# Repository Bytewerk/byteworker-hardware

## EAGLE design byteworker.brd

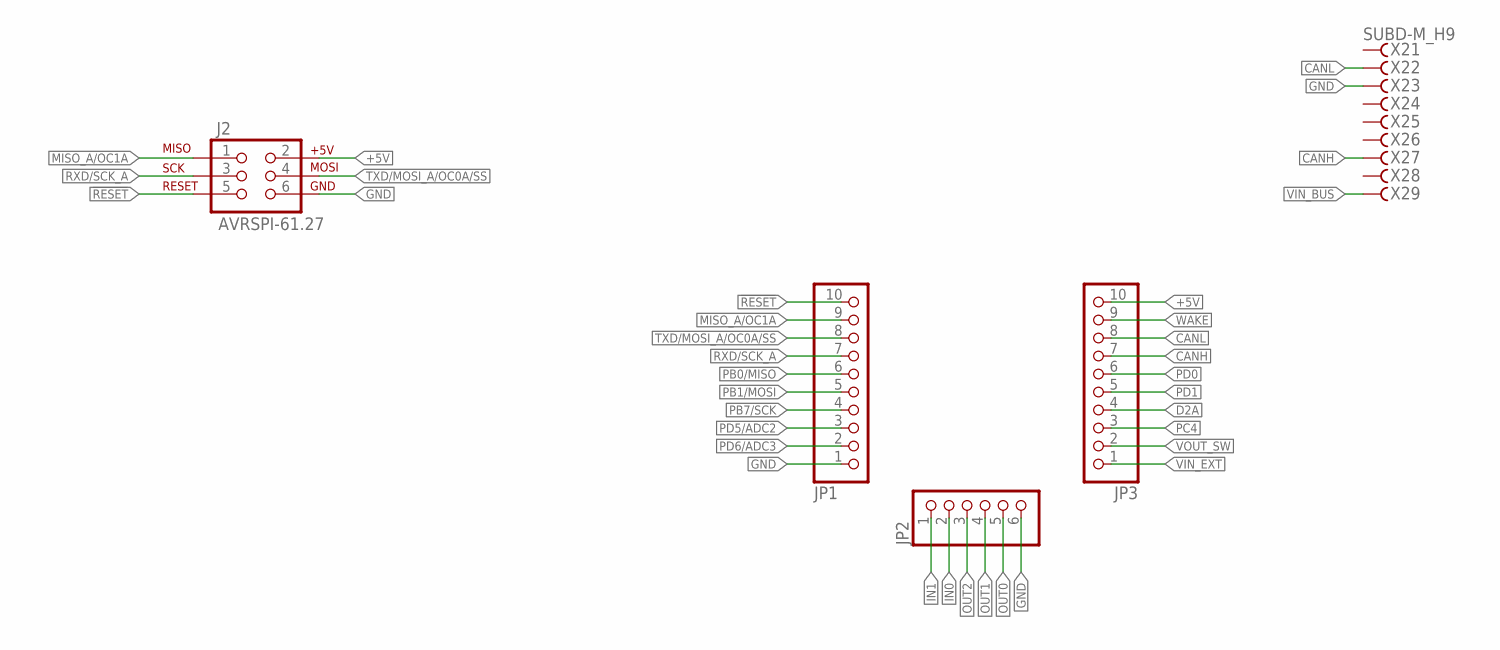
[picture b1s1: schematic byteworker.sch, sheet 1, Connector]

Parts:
J2: AVRSPI-61.27; 2X3-1.27
JP1, JP3: PINHD-1X10; 1X10
JP2: PINHD-1X6; 1X06
X2: SUBD-M_H9; SUBD9

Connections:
!RESET!: J2.5 (RESET), JP1.10; also elsewhere on the board
+5V: J2.2 (+5V), JP3.10; also elsewhere on the board
CANH: JP3.7, X2.8; also elsewhere on the board
CANL: JP3.8, X2.4; also elsewhere on the board
D2A: JP3.4; also elsewhere on the board
GND: J2.6 (GND), JP1.1, JP2.6, X2.3; also elsewhere on the board
IN0: JP2.2; also elsewhere on the board
IN1: JP2.1; also elsewhere on the board
MISO_A/OC1A: J2.1 (MISO), JP1.9; also elsewhere on the board
OUT0: JP2.5; also elsewhere on the board
OUT1: JP2.4; also elsewhere on the board
OUT2: JP2.3; also elsewhere on the board
PB0/MISO: JP1.6; also elsewhere on the board
PB1/MOSI: JP1.5; also elsewhere on the board
PB7/SCK: JP1.4; also elsewhere on the board
PC4: JP3.3; also elsewhere on the board
PD0: JP3.6; also elsewhere on the board
PD1: JP3.5; also elsewhere on the board
PD5/ADC2: JP1.3; also elsewhere on the board
PD6/ADC3: JP1.2; also elsewhere on the board
RXD/SCK_A: J2.3 (SCK), JP1.7; also elsewhere on the board
TXD/MOSI_A/OC0A/SS: J2.4 (MOSI), JP1.8; also elsewhere on the board
VIN_BUS: X2.6; also elsewhere on the board
VIN_EXT: JP3.1; also elsewhere on the board
VOUT_SW: JP3.2; also elsewhere on the board
WAKE: JP3.9; also elsewhere on the board

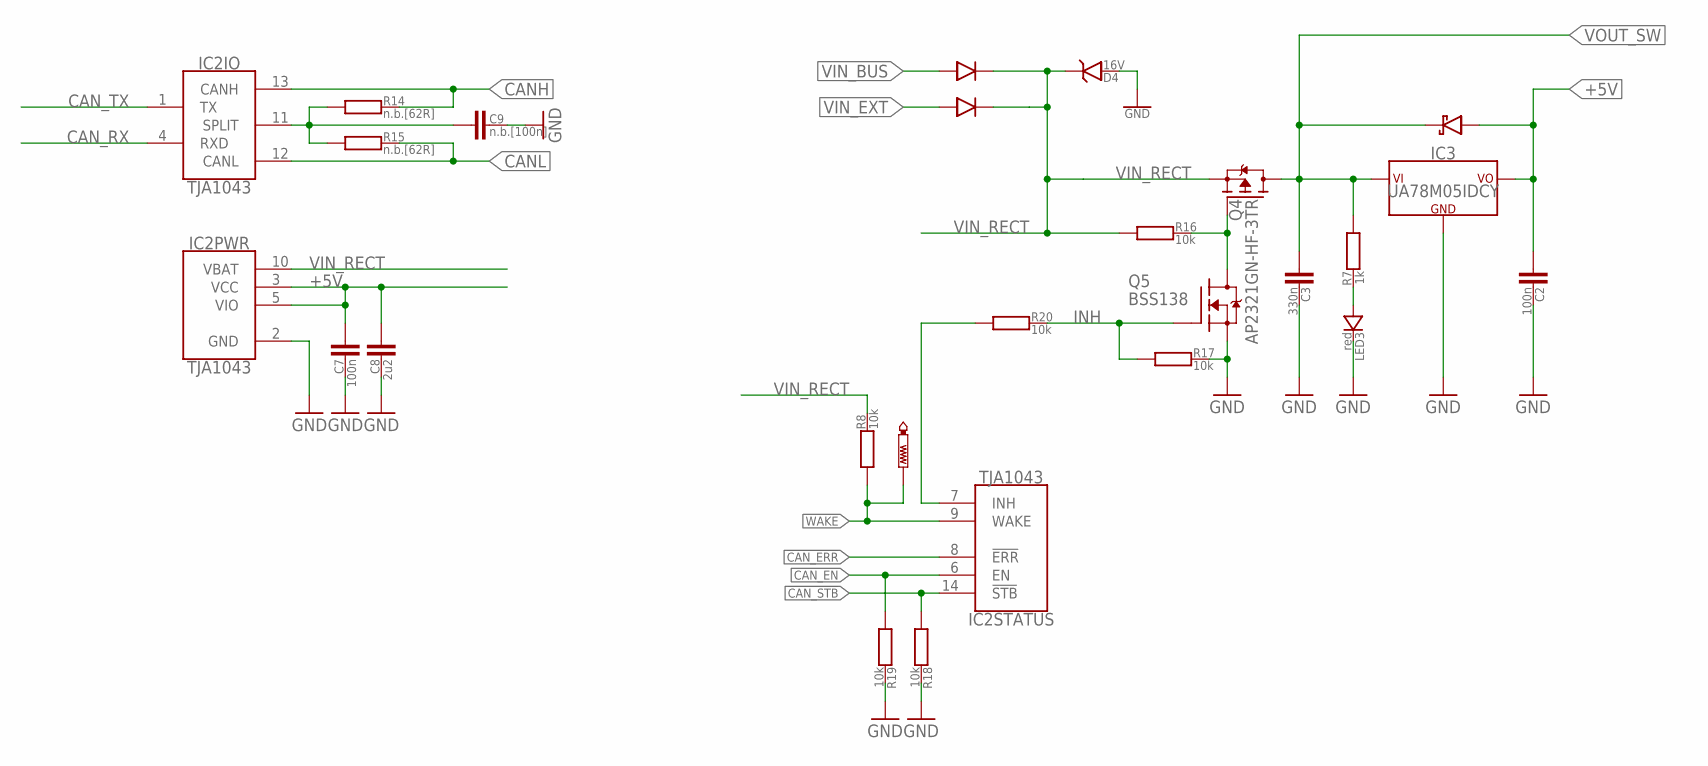
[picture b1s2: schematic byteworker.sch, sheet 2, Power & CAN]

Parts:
C2, C7: 100n; C0603
C3: 330n; C0603
C8: 2u2; C0805
C9: n.b.[100n]; C0603
D1, D5: 1N5819HW; SOD123
D4: 16V; SOD-128
D6: SCHOTTKY323; SOD323
IC2: TJA1043; SO14
IC3: UA78M05IDCY; SOT223
LED3: red; LED0603
Q4: AP2321GN-HF-3TR; SOT23-3
Q5: BSS138; SOT23C
R7: 1k; R0603
R8, R16, R17, R18, R19, R20: 10k; R0603
R14, R15: n.b.[62R]; R0603
TP2: PTR1B1,27; B1,27

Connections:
!CAN_ERR!: IC2.8 (!ERR!); also elsewhere on the board
!CAN_STB!: IC2.14 (!STB!), R18.1; also elsewhere on the board
+5V: C2.1, C7.1, C8.1, D6.A, IC2.3 (VCC), IC2.5 (VIO), IC3.3 (+5V); also elsewhere on the board
CANH: IC2.13 (CANH), R14.2; also elsewhere on the board
CANL: IC2.12 (CANL), R15.2; also elsewhere on the board
CAN_EN: IC2.6 (EN), R19.1; also elsewhere on the board
CAN_RX: IC2.4 (RXD); also elsewhere on the board
CAN_TX: IC2.1 (TX); also elsewhere on the board
GND: C2.2, C3.2, C7.2, C8.2, C9.2, D4.A, IC2.2 (GND), IC3.2 (GND), IC3.4 (GND), LED3.C, Q5.2 (S), R17.2, R18.2, R19.2; also elsewhere on the board
INH: Q5.1 (G), R17.1, R20.2
unnamed: C9.1, IC2.11 (SPLIT), R14.1, R15.1
unnamed: IC2.7 (INH), R20.1
unnamed: Q4.1 (G), Q5.3 (D), R16.2
unnamed: LED3.A, R7.2
VIN_BUS: D5.A; also elsewhere on the board
VIN_EXT: D1.A; also elsewhere on the board
VIN_RECT: D1.C, D4.C, D5.C, IC2.10 (VBAT), Q4.2 (S), R8.2, R16.1; also elsewhere on the board
VOUT_SW: C3.1, D6.C, IC3.1 (VIN), Q4.3 (D), R7.1; also elsewhere on the board
WAKE: IC2.9 (WAKE), R8.1, TP2.TP; also elsewhere on the board

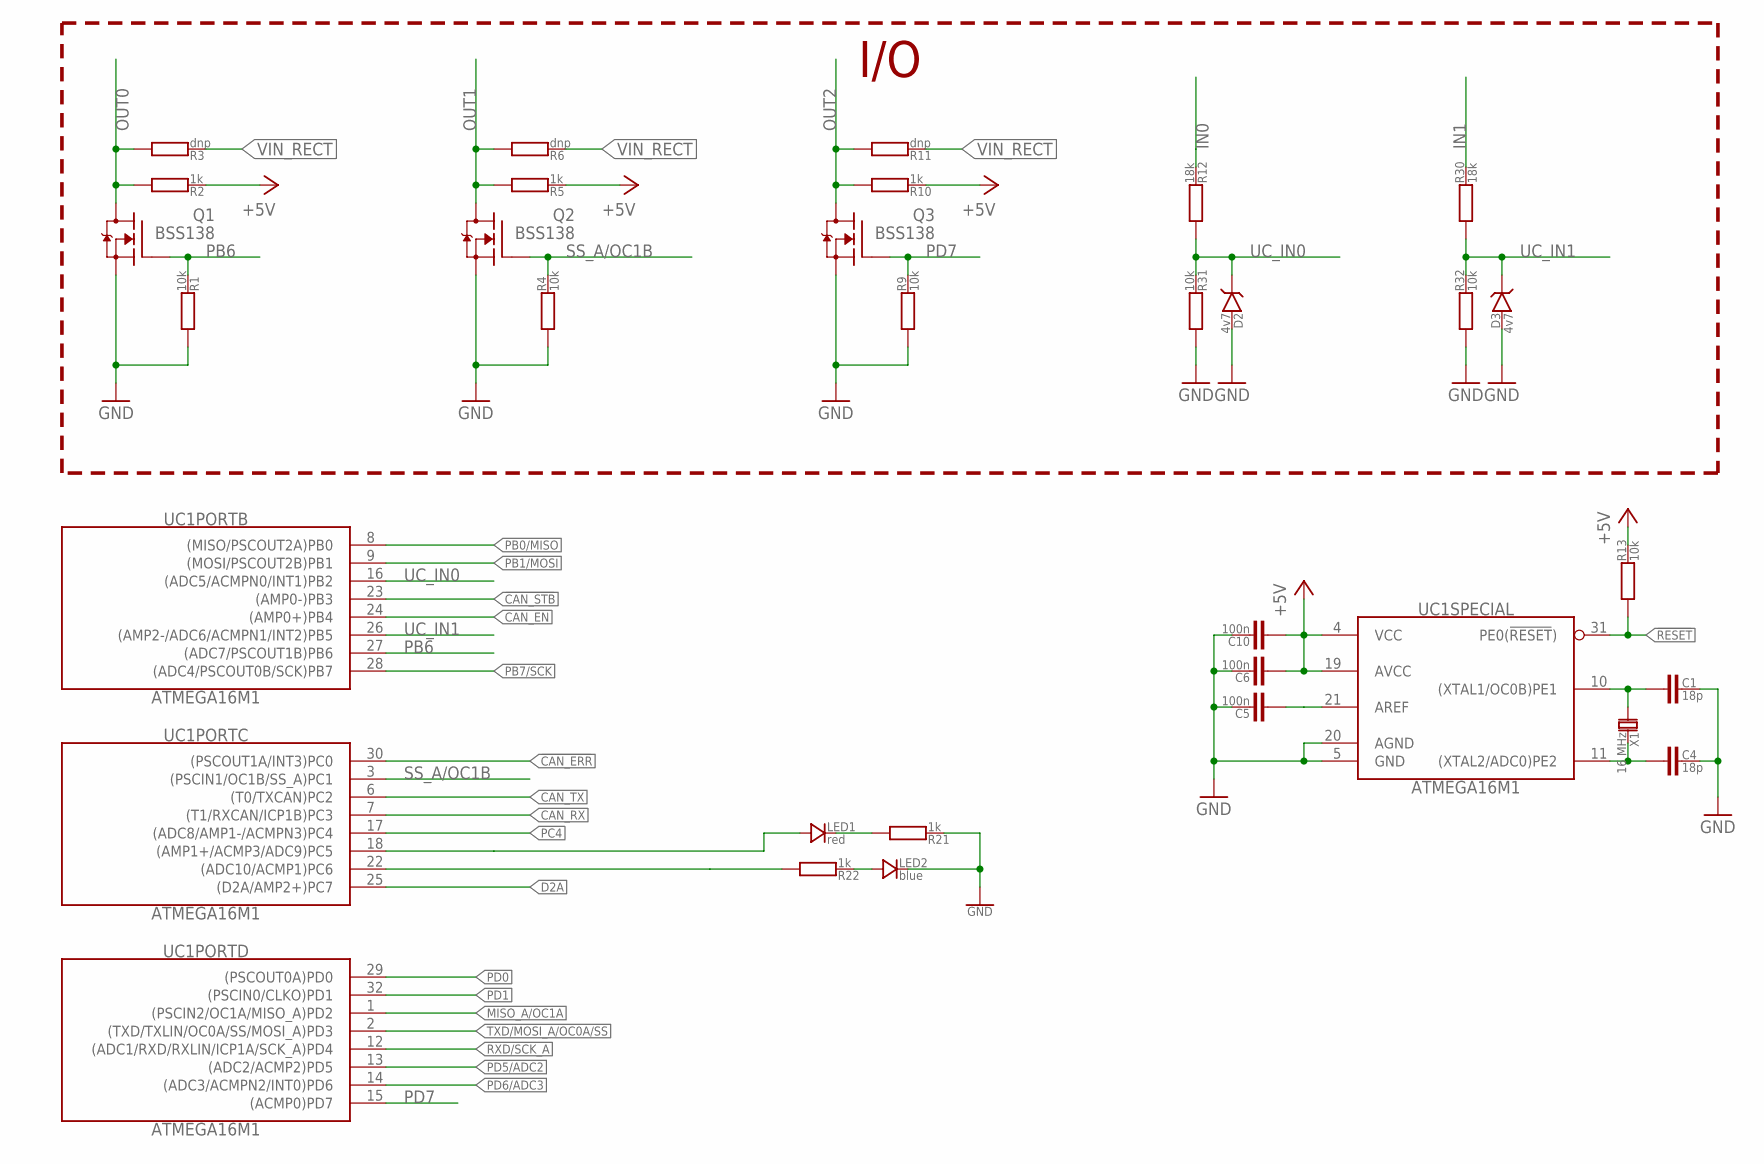
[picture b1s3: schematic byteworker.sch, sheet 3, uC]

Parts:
C1, C4: 18p; C0603
C5, C6, C10: 100n; C0603
D2, D3: 4v7; SOD80
LED1: red; LED0603
LED2: blue; LED0603
Q1, Q2, Q3: BSS138; SOT23C
R1, R4, R9, R13, R31, R32: 10k; R0603
R2, R5, R10, R21, R22: 1k; R0603
R3, R6, R11: dnp; R0603
R12, R30: 18k; R0603
UC1: ATMEGA16M1; TQFP32-08
X1: 16 MHz; 5.0X3.2

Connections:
!CAN_ERR!: UC1.30 ((PSCOUT1A/INT3)PC0); also elsewhere on the board
!CAN_STB!: UC1.23 ((AMP0-)PB3); also elsewhere on the board
!RESET!: R13.1, UC1.31 (PE0(!RESET!)); also elsewhere on the board
+5V: C6.1, C10.1, R2.2, R5.2, R10.2, R13.2, UC1.4 (VCC), UC1.19 (AVCC); also elsewhere on the board
AREF: C5.1, UC1.21 (AREF)
CAN_EN: UC1.24 ((AMP0+)PB4); also elsewhere on the board
CAN_RX: UC1.7 ((T1/RXCAN/ICP1B)PC3); also elsewhere on the board
CAN_TX: UC1.6 ((T0/TXCAN)PC2); also elsewhere on the board
D2A: UC1.25 ((D2A/AMP2+)PC7); also elsewhere on the board
GND: C1.2, C4.2, C5.2, C6.2, C10.2, D2.A, D3.A, LED2.C, Q1.2 (S), Q2.2 (S), Q3.2 (S), R1.1, R4.1, R9.1, R21.2, R31.1, R32.1, UC1.5 (GND), UC1.20 (AGND); also elsewhere on the board
IN0: R12.2; also elsewhere on the board
IN1: R30.2; also elsewhere on the board
MISO_A/OC1A: UC1.1 ((PSCIN2/OC1A/MISO_A)PD2); also elsewhere on the board
unnamed: C1.1, UC1.10 ((XTAL1/OC0B)PE1), X1.1
unnamed: C4.1, UC1.11 ((XTAL2/ADC0)PE2), X1.2
unnamed: LED2.A, R22.2
unnamed: LED1.A, UC1.18 ((AMP1+/ACMP3/ADC9)PC5)
unnamed: LED1.C, R21.1
OUT0: Q1.3 (D), R2.1, R3.1; also elsewhere on the board
OUT1: Q2.3 (D), R5.1, R6.1; also elsewhere on the board
OUT2: Q3.3 (D), R10.1, R11.1; also elsewhere on the board
PB0/MISO: UC1.8 ((MISO/PSCOUT2A)PB0); also elsewhere on the board
PB1/MOSI: UC1.9 ((MOSI/PSCOUT2B)PB1); also elsewhere on the board
PB6: Q1.1 (G), R1.2, UC1.27 ((ADC7/PSCOUT1B)PB6)
PB7/SCK: UC1.28 ((ADC4/PSCOUT0B/SCK)PB7); also elsewhere on the board
PC4: UC1.17 ((ADC8/AMP1-/ACMPN3)PC4); also elsewhere on the board
PD0: UC1.29 ((PSCOUT0A)PD0); also elsewhere on the board
PD1: UC1.32 ((PSCIN0/CLKO)PD1); also elsewhere on the board
PD5/ADC2: UC1.13 ((ADC2/ACMP2)PD5); also elsewhere on the board
PD6/ADC3: UC1.14 ((ADC3/ACMPN2/INT0)PD6); also elsewhere on the board
PD7: Q3.1 (G), R9.2, UC1.15 ((ACMP0)PD7)
RXD/SCK_A: UC1.12 ((ADC1/RXD/RXLIN/ICP1A/SCK_A)PD4); also elsewhere on the board
SS_A/OC1B: Q2.1 (G), R4.2, UC1.3 ((PSCIN1/OC1B/SS_A)PC1)
TESTLED2: R22.1, UC1.22 ((ADC10/ACMP1)PC6)
TXD/MOSI_A/OC0A/SS: UC1.2 ((TXD/TXLIN/OC0A/SS/MOSI_A)PD3); also elsewhere on the board
UC_IN0: D2.C, R12.1, R31.2, UC1.16 ((ADC5/ACMPN0/INT1)PB2)
UC_IN1: D3.C, R30.1, R32.2, UC1.26 ((AMP2-/ADC6/ACMPN1/INT2)PB5)
VIN_RECT: R3.2, R6.2, R11.2; also elsewhere on the board

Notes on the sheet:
I/O

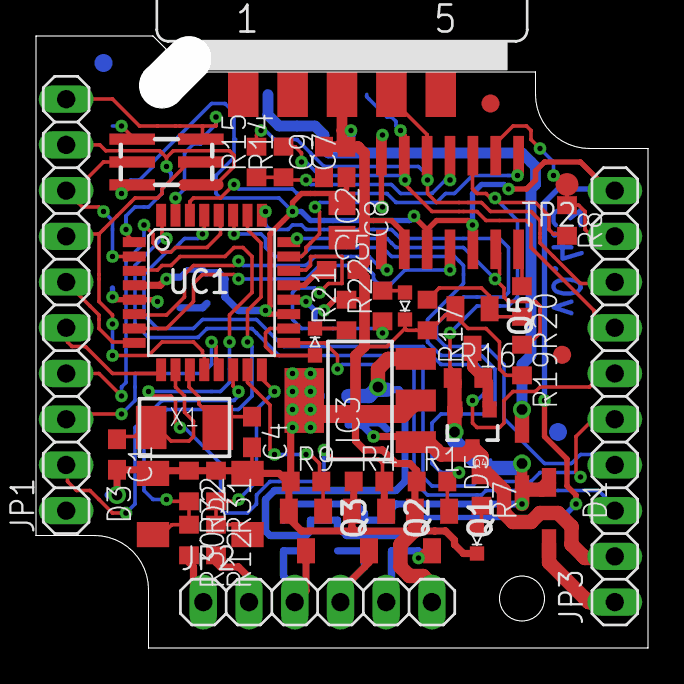
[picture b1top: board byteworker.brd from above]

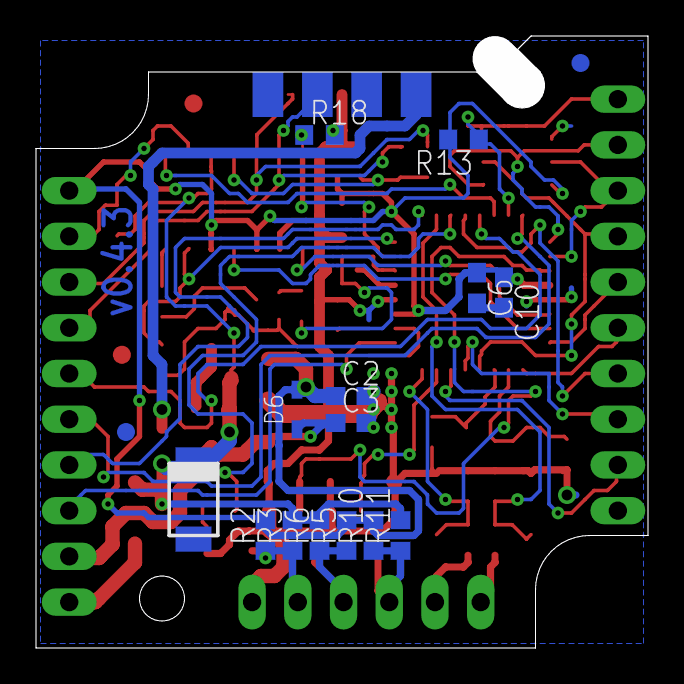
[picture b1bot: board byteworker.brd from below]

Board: 2 copper layers, 34.0 x 34.0 mm, 63 parts (16 on the bottom side), 49 nets.

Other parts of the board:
U$2, U$4, U$5, U$6: FIDUCIAL_R

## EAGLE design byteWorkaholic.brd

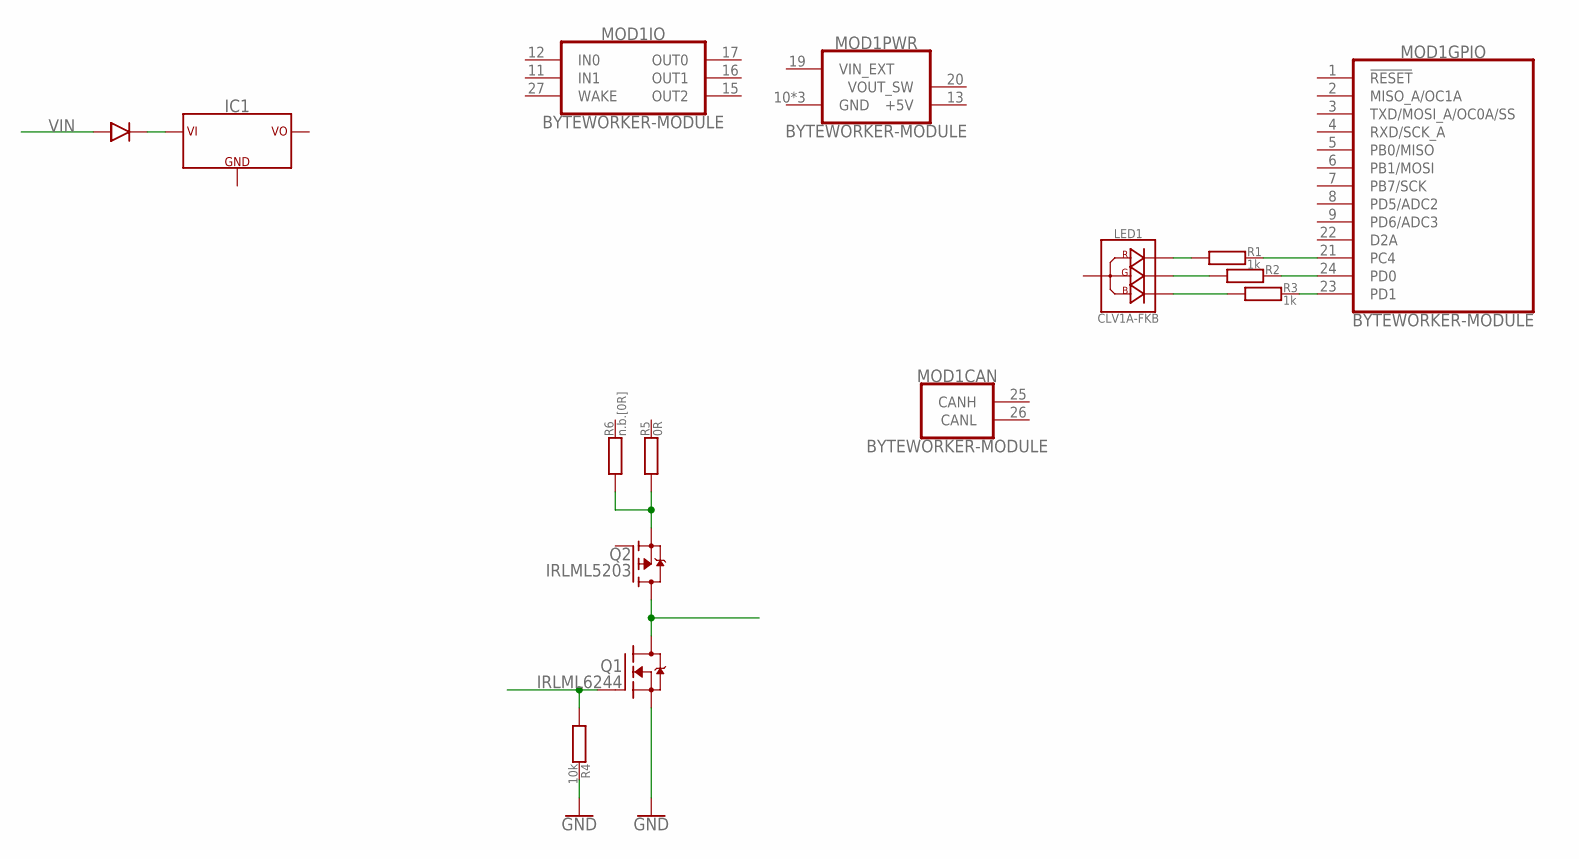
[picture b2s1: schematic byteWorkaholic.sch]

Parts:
D1: 1N5819HW; SOD123
IC1: OKI-H
LED1: CLV1A-FKB
MOD1: BYTEWORKER-MODULE
Q1: IRLML6244; SOT23
Q2: IRLML5203; SOT23
R1, R3: 1k; R0603
R2: R0603
R4: 10k; R0603
R5: 0R; R0603
R6: n.b.[0R]; R0603

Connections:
GND: IC1.2 (GND), MOD1.10 (GND), MOD1.18 (GND), MOD1.28 (GND), Q1.2 (S), R4.2
unnamed: LED1.R (R_C), R1.1
unnamed: LED1.G (G_C), R2.1
unnamed: LED1.B (B_C), R3.1
unnamed: MOD1.23 (PD1), R3.2
unnamed: MOD1.24 (PD0), R2.2
unnamed: MOD1.21 (PC4), R1.2
unnamed: D1.C, IC1.1 (VIN)
unnamed: Q1.3 (D), Q2.3 (D)
unnamed: Q1.1 (G), R4.1
unnamed: Q2.2 (S), R5.1, R6.1
VIN: D1.A
VIN_EXT: MOD1.19 (VIN_EXT)
VOUT_SW: MOD1.20 (VOUT_SW)

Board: 2 copper layers, 12 parts (0 on the bottom side), 11 nets, no tracks yet.

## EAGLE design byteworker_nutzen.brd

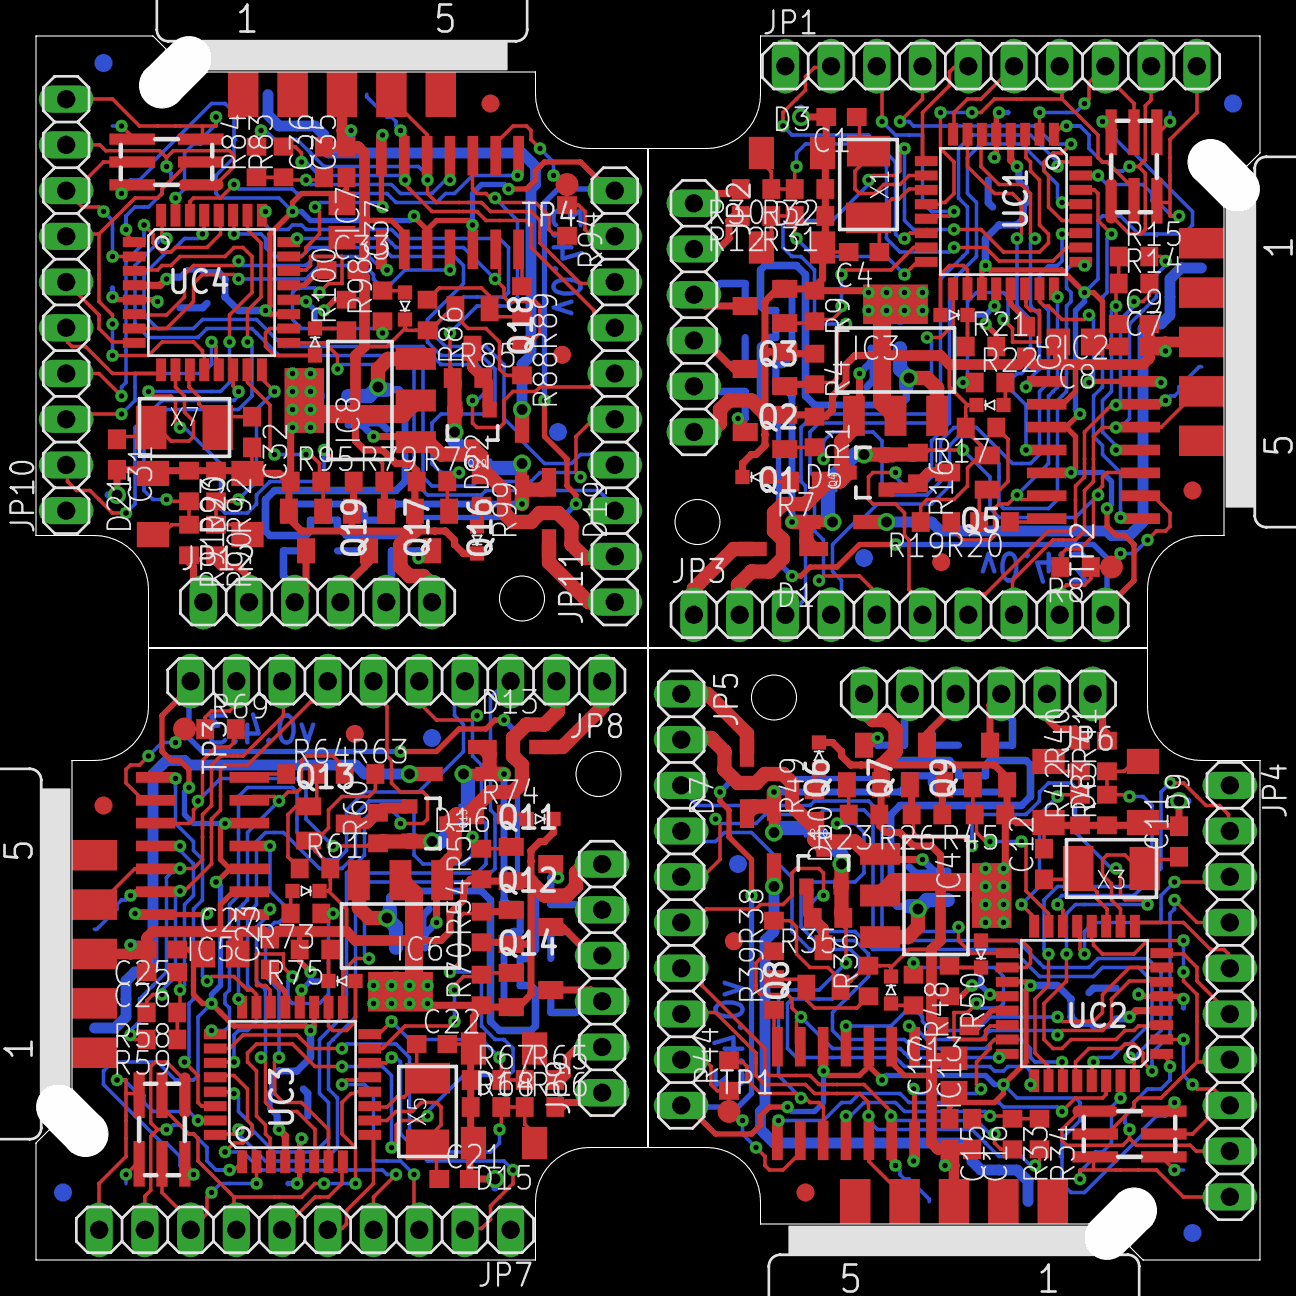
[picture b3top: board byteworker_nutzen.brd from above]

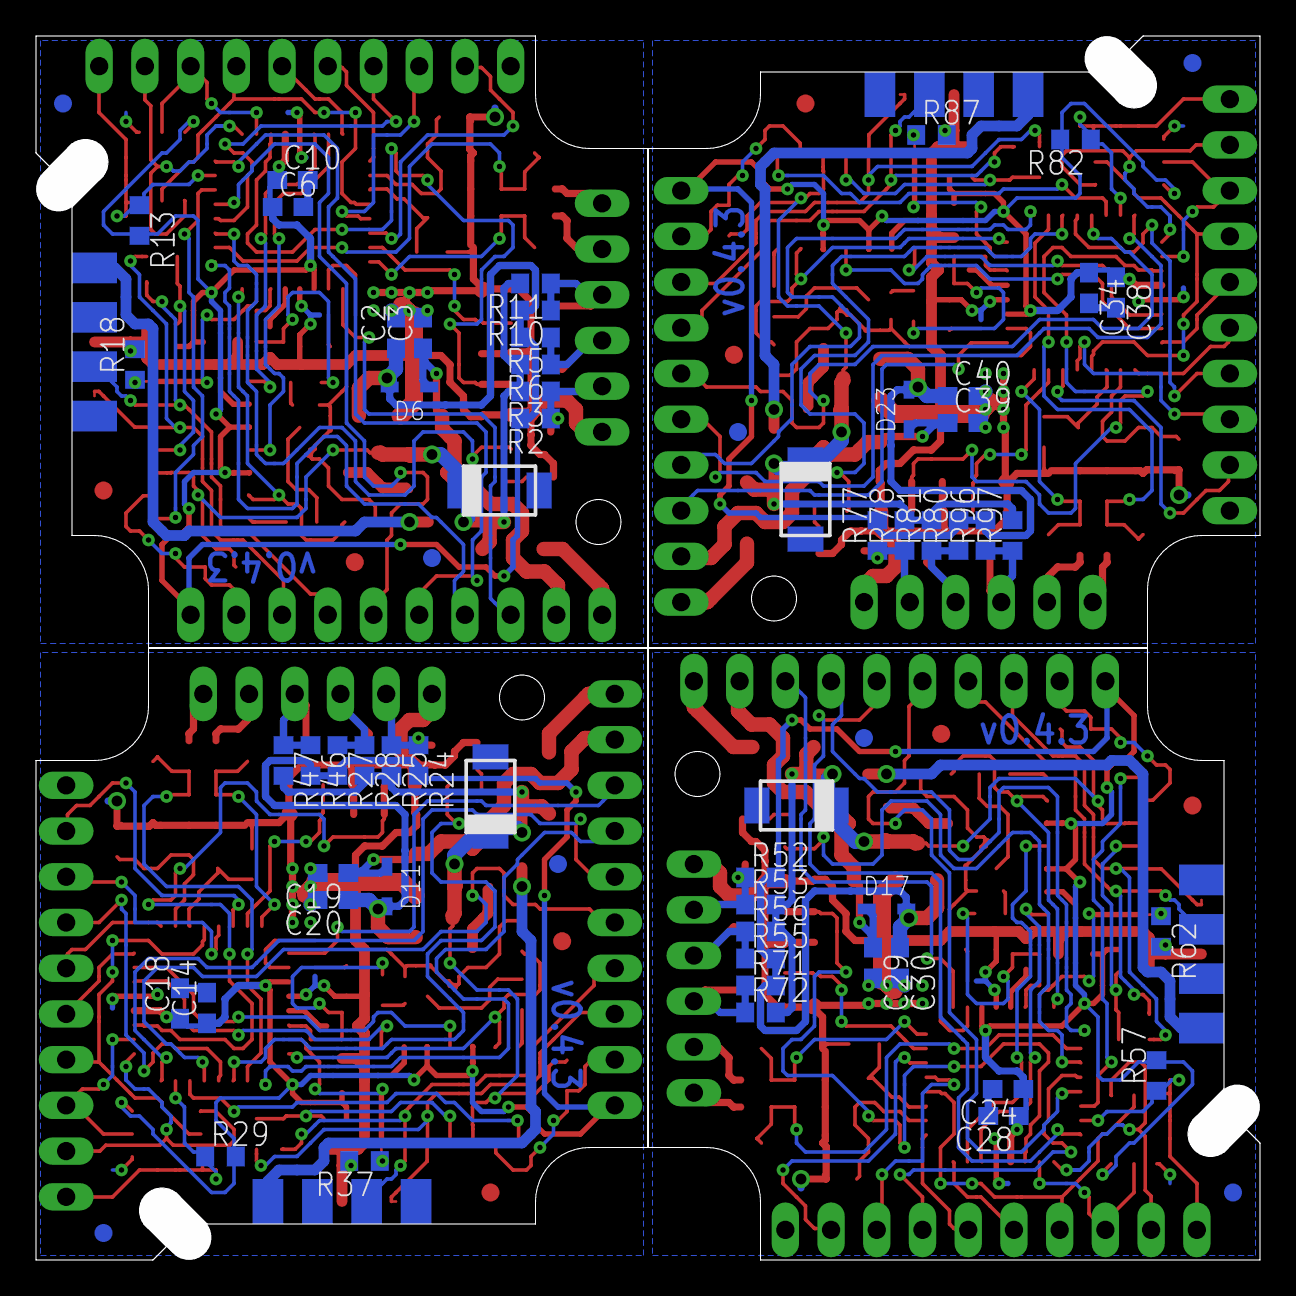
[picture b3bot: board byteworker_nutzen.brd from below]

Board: 2 copper layers, 68.0 x 68.0 mm, 258 parts (64 on the bottom side), 196 nets.

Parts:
C1, C4, C11, C12, C21, C22, C31, C32: 18p; C0603
C2, C5, C6, C7, C10, C13, C14, C15, C18, C20, C23, C24, C25, C28, C30, C33, C34, C35, C38, C40: 100n; C0603
C3, C19, C29, C39: 330n; C0603
C8, C17, C27, C37: 2u2; C0805
C9, C16, C26, C36: n.b.[100n]; C0603
D1, D5, D7, D10, D13, D16, D19, D22: 1N5819HW; SOD123
D2, D3, D8, D9, D14, D15, D20, D21: 4v7; SOD80
D4, D12, D18, D24: 16V; SOD-128
D6, D11, D17, D23: SCHOTTKY323; SOD323
E$1, E$2, E$3, E$4: MILL-MARKER
E$5, E$6: SCRATCH-MARKER
IC1, IC2, IC5, IC7: TJA1043; SO14
IC3, IC4, IC6, IC8: UA78M05IDCY; SOT223
J1, J2, J3, J4: AVRSPI-61.27; 2X3-1.27
JP1, JP3, JP4, JP5, JP7, JP8, JP10, JP11: 1X10
JP2, JP6, JP9, JP12: 1X06
LED1, LED3, LED5, LED6, LED8, LED9, LED11, LED12: red; LED0603
LED2, LED4, LED7, LED10: blue; LED0603
Q1, Q2, Q3, Q5, Q6, Q7, Q8, Q9, Q11, Q12, Q13, Q14, Q16, Q17, Q18, Q19: BSS138; SOT23C
Q4, Q10, Q15, Q20: AP2321GN-HF-3TR; SOT23-3
R1, R4, R8, R9, R13, R16, R17, R18, R19, R20, R23, R26, R29, R31, R32, R35, R36, R37, R38, R39, R42, R43, R44, R45, R51, R54, R57, R60, R61, R62, R63, R64, R67, R68, R69, R70, R76, R79, R82, R85, R86, R87, R88, R89, R92, R93, R94, R95: 10k; R0603
R2, R5, R7, R10, R21, R22, R24, R27, R46, R48, R49, R50, R52, R55, R71, R73, R74, R75, R77, R80, R96, R98, R99, R100: 1k; R0603
R3, R6, R11, R25, R28, R47, R53, R56, R72, R78, R81, R97: dnp; R0603
R12, R30, R40, R41, R65, R66, R90, R91: 18k; R0603
R14, R15, R33, R34, R58, R59, R83, R84: n.b.[62R]; R0603
TP1, TP2, TP3, TP4: PTR1B1,27; B1,27
U$1, U$2, U$3, U$4, U$5, U$6, U$7, U$8, U$9, U$10, U$11, U$12, U$13, U$14, U$15, U$16: FIDUCIAL_R
UC1, UC2, UC3, UC4: ATMEGA16M1; TQFP32-08
X1, X3, X5, X7: 16 MHz; 5.0X3.2
X2, X4, X6, X8: SUBD-M_H9; SUBD9

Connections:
!CAN_ERR!: IC2.8, UC1.30
!CAN_ERR!1: IC1.8, UC2.30
!CAN_ERR!2: IC5.8, UC3.30
!CAN_ERR!3: IC7.8, UC4.30
!CAN_STB!: IC2.14, R18.1, UC1.23
!CAN_STB!1: IC1.14, R37.1, UC2.23
!CAN_STB!2: IC5.14, R62.1, UC3.23
!CAN_STB!3: IC7.14, R87.1, UC4.23
!RESET!: J2.5, JP1.10, R13.1, UC1.31
!RESET!1: J1.5, JP4.10, R29.1, UC2.31
!RESET!2: J3.5, JP7.10, R57.1, UC3.31
!RESET!3: J4.5, JP10.10, R82.1, UC4.31
+5V: C2.1, C6.1, C7.1, C8.1, C10.1, D6.A, IC2.3, IC2.5, IC3.3, J2.2, JP3.10, R2.2, R5.2, R10.2, R13.2, UC1.4, UC1.19
+5V1: C14.1, C15.1, C17.1, C18.1, C20.1, D11.A, IC1.3, IC1.5, IC4.3, J1.2, JP5.10, R24.2, R27.2, R29.2, R46.2, UC2.4, UC2.19
+5V2: C24.1, C25.1, C27.1, C28.1, C30.1, D17.A, IC5.3, IC5.5, IC6.3, J3.2, JP8.10, R52.2, R55.2, R57.2, R71.2, UC3.4, UC3.19
+5V3: C34.1, C35.1, C37.1, C38.1, C40.1, D23.A, IC7.3, IC7.5, IC8.3, J4.2, JP11.10, R77.2, R80.2, R82.2, R96.2, UC4.4, UC4.19
AREF: C5.1, UC1.21
AREF1: C13.1, UC2.21
AREF2: C23.1, UC3.21
AREF3: C33.1, UC4.21
CANH: IC2.13, JP3.7, R14.2, X2.8
CANH1: IC1.13, JP5.7, R33.2, X4.8
CANH2: IC5.13, JP8.7, R58.2, X6.8
CANH3: IC7.13, JP11.7, R83.2, X8.8
CANL: IC2.12, JP3.8, R15.2, X2.4
CANL1: IC1.12, JP5.8, R34.2, X4.4
CANL2: IC5.12, JP8.8, R59.2, X6.4
CANL3: IC7.12, JP11.8, R84.2, X8.4
CAN_EN: IC2.6, R19.1, UC1.24
CAN_EN1: IC1.6, R38.1, UC2.24
CAN_EN2: IC5.6, R63.1, UC3.24
CAN_EN3: IC7.6, R88.1, UC4.24
CAN_RX: IC2.4, UC1.7
CAN_RX1: IC1.4, UC2.7
CAN_RX2: IC5.4, UC3.7
CAN_RX3: IC7.4, UC4.7
CAN_TX: IC2.1, UC1.6
CAN_TX1: IC1.1, UC2.6
CAN_TX2: IC5.1, UC3.6
CAN_TX3: IC7.1, UC4.6
D2A: JP3.4, UC1.25
D2A1: JP5.4, UC2.25
D2A2: JP8.4, UC3.25
D2A3: JP11.4, UC4.25
GND: C1.2, C2.2, C3.2, C4.2, C5.2, C6.2, C7.2, C8.2, C9.2, C10.2, D2.A, D3.A, D4.A, IC2.2, IC3.2, IC3.4, J2.6, JP1.1, JP2.6, LED2.C, LED3.C, Q1.2, Q2.2, Q3.2, Q5.2, R1.1, R4.1, R9.1, R17.2, R18.2, R19.2, R21.2, R31.1, R32.1, UC1.5, UC1.20, X2.3
GND1: C11.2, C12.2, C13.2, C14.2, C15.2, C16.2, C17.2, C18.2, C19.2, C20.2, D8.A, D9.A, D12.A, IC1.2, IC4.2, IC4.4, J1.6, JP4.1, JP6.6, LED4.C, LED5.C, Q6.2, Q7.2, Q8.2, Q9.2, R23.1, R26.1, R36.2, R37.2, R38.2, R42.1, R43.1, R45.1, R50.2, UC2.5, UC2.20, X4.3
GND2: C21.2, C22.2, C23.2, C24.2, C25.2, C26.2, C27.2, C28.2, C29.2, C30.2, D14.A, D15.A, D18.A, IC5.2, IC6.2, IC6.4, J3.6, JP7.1, JP9.6, LED7.C, LED8.C, Q11.2, Q12.2, Q13.2, Q14.2, R51.1, R54.1, R61.2, R62.2, R63.2, R67.1, R68.1, R70.1, R75.2, UC3.5, UC3.20, X6.3
GND3: C31.2, C32.2, C33.2, C34.2, C35.2, C36.2, C37.2, C38.2, C39.2, C40.2, D20.A, D21.A, D24.A, IC7.2, IC8.2, IC8.4, J4.6, JP10.1, JP12.6, LED10.C, LED11.C, Q16.2, Q17.2, Q18.2, Q19.2, R76.1, R79.1, R86.2, R87.2, R88.2, R92.1, R93.1, R95.1, R100.2, UC4.5, UC4.20, X8.3
IN0: JP2.2, R12.2
IN1: JP2.1, R30.2
IN2: JP6.1, R41.2
IN3: JP6.2, R40.2
IN4: JP9.1, R66.2
IN5: JP9.2, R65.2
IN6: JP12.1, R91.2
IN7: JP12.2, R90.2
INH: Q5.1, R17.1, R20.2
INH1: Q8.1, R36.1, R39.2
INH2: Q13.1, R61.1, R64.2
INH3: Q18.1, R86.1, R89.2
MISO_A/OC1A: J2.1, JP1.9, UC1.1
MISO_A/OC1A1: J1.1, JP4.9, UC2.1
MISO_A/OC1A2: J3.1, JP7.9, UC3.1
MISO_A/OC1A3: J4.1, JP10.9, UC4.1
unnamed: C1.1, UC1.10, X1.1
unnamed: C4.1, UC1.11, X1.2
unnamed: LED2.A, R22.2
unnamed: C9.1, IC2.11, R14.1, R15.1
unnamed: IC2.7, R20.1
unnamed: Q4.1, Q5.3, R16.2
unnamed: LED1.A, UC1.18
unnamed: LED3.A, R7.2
unnamed: LED1.C, R21.1
unnamed: C11.1, UC2.10, X3.1
unnamed: C12.1, UC2.11, X3.2
unnamed: Q8.3, Q10.1, R35.2
unnamed: C16.1, IC1.11, R33.1, R34.1
unnamed: IC1.7, R39.1
unnamed: LED4.A, R48.2
unnamed: LED5.A, R49.2
unnamed: LED6.A, UC2.18
unnamed: LED6.C, R50.1
unnamed: C21.1, UC3.10, X5.1
unnamed: C22.1, UC3.11, X5.2
unnamed: Q13.3, Q15.1, R60.2
unnamed: C26.1, IC5.11, R58.1, R59.1
unnamed: IC5.7, R64.1
unnamed: LED7.A, R73.2
unnamed: LED8.A, R74.2
unnamed: LED9.A, UC3.18
unnamed: LED9.C, R75.1
unnamed: C31.1, UC4.10, X7.1
unnamed: C32.1, UC4.11, X7.2
unnamed: Q18.3, Q20.1, R85.2
unnamed: C36.1, IC7.11, R83.1, R84.1
unnamed: IC7.7, R89.1
unnamed: LED10.A, R98.2
unnamed: LED11.A, R99.2
unnamed: LED12.A, UC4.18
unnamed: LED12.C, R100.1
OUT0: JP2.5, Q1.3, R2.1, R3.1
OUT1: JP2.4, Q2.3, R5.1, R6.1
OUT2: JP2.3, Q3.3, R10.1, R11.1
OUT3: JP6.4, Q7.3, R27.1, R28.1
OUT4: JP6.5, Q6.3, R24.1, R25.1
OUT5: JP6.3, Q9.3, R46.1, R47.1
OUT6: JP9.4, Q12.3, R55.1, R56.1
OUT7: JP9.5, Q11.3, R52.1, R53.1
OUT8: JP9.3, Q14.3, R71.1, R72.1
OUT9: JP12.4, Q17.3, R80.1, R81.1
OUT10: JP12.5, Q16.3, R77.1, R78.1
OUT11: JP12.3, Q19.3, R96.1, R97.1
PB0/MISO: JP1.6, UC1.8
PB0/MISO1: JP4.6, UC2.8
PB0/MISO2: JP7.6, UC3.8
PB0/MISO3: JP10.6, UC4.8
PB1: Q6.1, R23.2, UC2.27
PB1/MOSI: JP1.5, UC1.9
PB1/MOSI1: JP4.5, UC2.9
PB1/MOSI2: JP7.5, UC3.9
PB1/MOSI3: JP10.5, UC4.9
PB2: Q11.1, R51.2, UC3.27
PB3: Q16.1, R76.2, UC4.27
PB6: Q1.1, R1.2, UC1.27
PB7/SCK: JP1.4, UC1.28
PB7/SCK1: JP4.4, UC2.28
PB7/SCK2: JP7.4, UC3.28
PB7/SCK3: JP10.4, UC4.28
PC1: JP5.3, UC2.17
PC2: JP8.3, UC3.17
PC3: JP11.3, UC4.17
PC4: JP3.3, UC1.17
PD0: JP3.6, UC1.29
PD1: JP3.5, UC1.32
PD2: Q9.1, R45.2, UC2.15
PD3: JP5.5, UC2.32
PD4: JP5.6, UC2.29
PD5: Q14.1, R70.2, UC3.15
PD5/ADC1: JP4.3, UC2.13
PD5/ADC2: JP1.3, UC1.13
PD5/ADC3: JP7.3, UC3.13
PD5/ADC4: JP10.3, UC4.13
PD6: JP8.5, UC3.32
PD6/ADC1: JP4.2, UC2.14
PD6/ADC2: JP7.2, UC3.14
PD6/ADC3: JP1.2, UC1.14
PD6/ADC4: JP10.2, UC4.14
PD7: Q3.1, R9.2, UC1.15
PD8: JP8.6, UC3.29
PD9: Q19.1, R95.2, UC4.15
PD10: JP11.5, UC4.32
PD11: JP11.6, UC4.29
RXD/SCK_A: J2.3, JP1.7, UC1.12
RXD/SCK_A1: J1.3, JP4.7, UC2.12
RXD/SCK_A2: J3.3, JP7.7, UC3.12
RXD/SCK_A3: J4.3, JP10.7, UC4.12
SS_A/OC1B: Q2.1, R4.2, UC1.3
SS_A/OC1B1: Q7.1, R26.2, UC2.3
SS_A/OC1B2: Q12.1, R54.2, UC3.3
SS_A/OC1B3: Q17.1, R79.2, UC4.3
TESTLED1: R48.1, UC2.22
TESTLED2: R22.1, UC1.22
TESTLED3: R73.1, UC3.22
TESTLED4: R98.1, UC4.22
TXD/MOSI_A/OC0A/SS: J2.4, JP1.8, UC1.2
TXD/MOSI_A/OC0A/SS1: J1.4, JP4.8, UC2.2
TXD/MOSI_A/OC0A/SS2: J3.4, JP7.8, UC3.2
TXD/MOSI_A/OC0A/SS3: J4.4, JP10.8, UC4.2
UC_IN0: D2.C, R12.1, R31.2, UC1.16
UC_IN1: D3.C, R30.1, R32.2, UC1.26
UC_IN2: D8.C, R40.1, R42.2, UC2.16
UC_IN3: D9.C, R41.1, R43.2, UC2.26
UC_IN4: D14.C, R65.1, R67.2, UC3.16
UC_IN5: D15.C, R66.1, R68.2, UC3.26
UC_IN6: D20.C, R90.1, R92.2, UC4.16
UC_IN7: D21.C, R91.1, R93.2, UC4.26
VIN_BUS: D5.A, X2.6
VIN_BUS1: D10.A, X4.6
VIN_BUS2: D16.A, X6.6
VIN_BUS3: D22.A, X8.6
VIN_EXT: D1.A, JP3.1
VIN_EXT1: D7.A, JP5.1
VIN_EXT2: D13.A, JP8.1
VIN_EXT3: D19.A, JP11.1
VIN_RECT: D1.C, D4.C, D5.C, IC2.10, Q4.2, R3.2, R6.2, R8.2, R11.2, R16.1
VIN_RECT1: D7.C, D10.C, D12.C, IC1.10, Q10.2, R25.2, R28.2, R35.1, R44.2, R47.2
VIN_RECT2: D13.C, D16.C, D18.C, IC5.10, Q15.2, R53.2, R56.2, R60.1, R69.2, R72.2
VIN_RECT3: D19.C, D22.C, D24.C, IC7.10, Q20.2, R78.2, R81.2, R85.1, R94.2, R97.2
VOUT_SW: C3.1, D6.C, IC3.1, JP3.2, Q4.3, R7.1
VOUT_SW1: C19.1, D11.C, IC4.1, JP5.2, Q10.3, R49.1
VOUT_SW2: C29.1, D17.C, IC6.1, JP8.2, Q15.3, R74.1
VOUT_SW3: C39.1, D23.C, IC8.1, JP11.2, Q20.3, R99.1
WAKE: IC2.9, JP3.9, R8.1, TP2.TP
WAKE1: IC1.9, JP5.9, R44.1, TP1.TP
WAKE2: IC5.9, JP8.9, R69.1, TP3.TP
WAKE3: IC7.9, JP11.9, R94.1, TP4.TP

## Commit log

2014-08-16 Init
2014-10-13 unknown changes on IC2
2014-10-13 - 3rd output fet - moved one ISP pin away from output FET - larger connector with additional ground - larger capacitors - lower part count
2014-11-08 - minor changes to schemanics - placement done(brd)
2014-11-08 - Shuffle some pins - Optional wake on input pins
2014-11-10 - Some fixes in the schematics suggested by struppi - an incomplete board layout
2014-11-11 Layout finish
2014-11-13 v0.2: - Changed resistor values - Re-aligned pinheaders
2014-11-14 byteWorkaholic: unfinished motherboard for the byteworker: INIT
2014-11-18 more current for 12V_SW (0.8mm tracks)
2015-03-17 Done routing
2015-04-29 v0.3.0: - swap subD connector for Male version. - center subD connector
2015-06-09 v0.4.0: - 500 mA +5V voltage regulator with larger package and input voltage - female sub-d connector - thicker power traces - removed 1 test-led
2015-06-12 v4.1: add 2nd test LED
2015-06-12 v0.4.2: thicker input tracks to balance in and outgoing currunt
2015-06-20 v0.4.3: - minor changes to make milling more obvious
2015-06-20 script to auto-generate a nutzen
2015-06-20 remove byteworkaholic
2015-06-20 renamed .hgignore to .gitignore
2015-06-20 adapt .gitignore to new format
2015-06-20 add generated nutzen to repository
2015-06-20 force include of bytework symbol lib in panel generation script

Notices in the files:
parts and their libraries:
bytewerk-frames: Creative Commons 3.0 CC-BY-SA
bytewerk-crystal: CC-BY-SA
